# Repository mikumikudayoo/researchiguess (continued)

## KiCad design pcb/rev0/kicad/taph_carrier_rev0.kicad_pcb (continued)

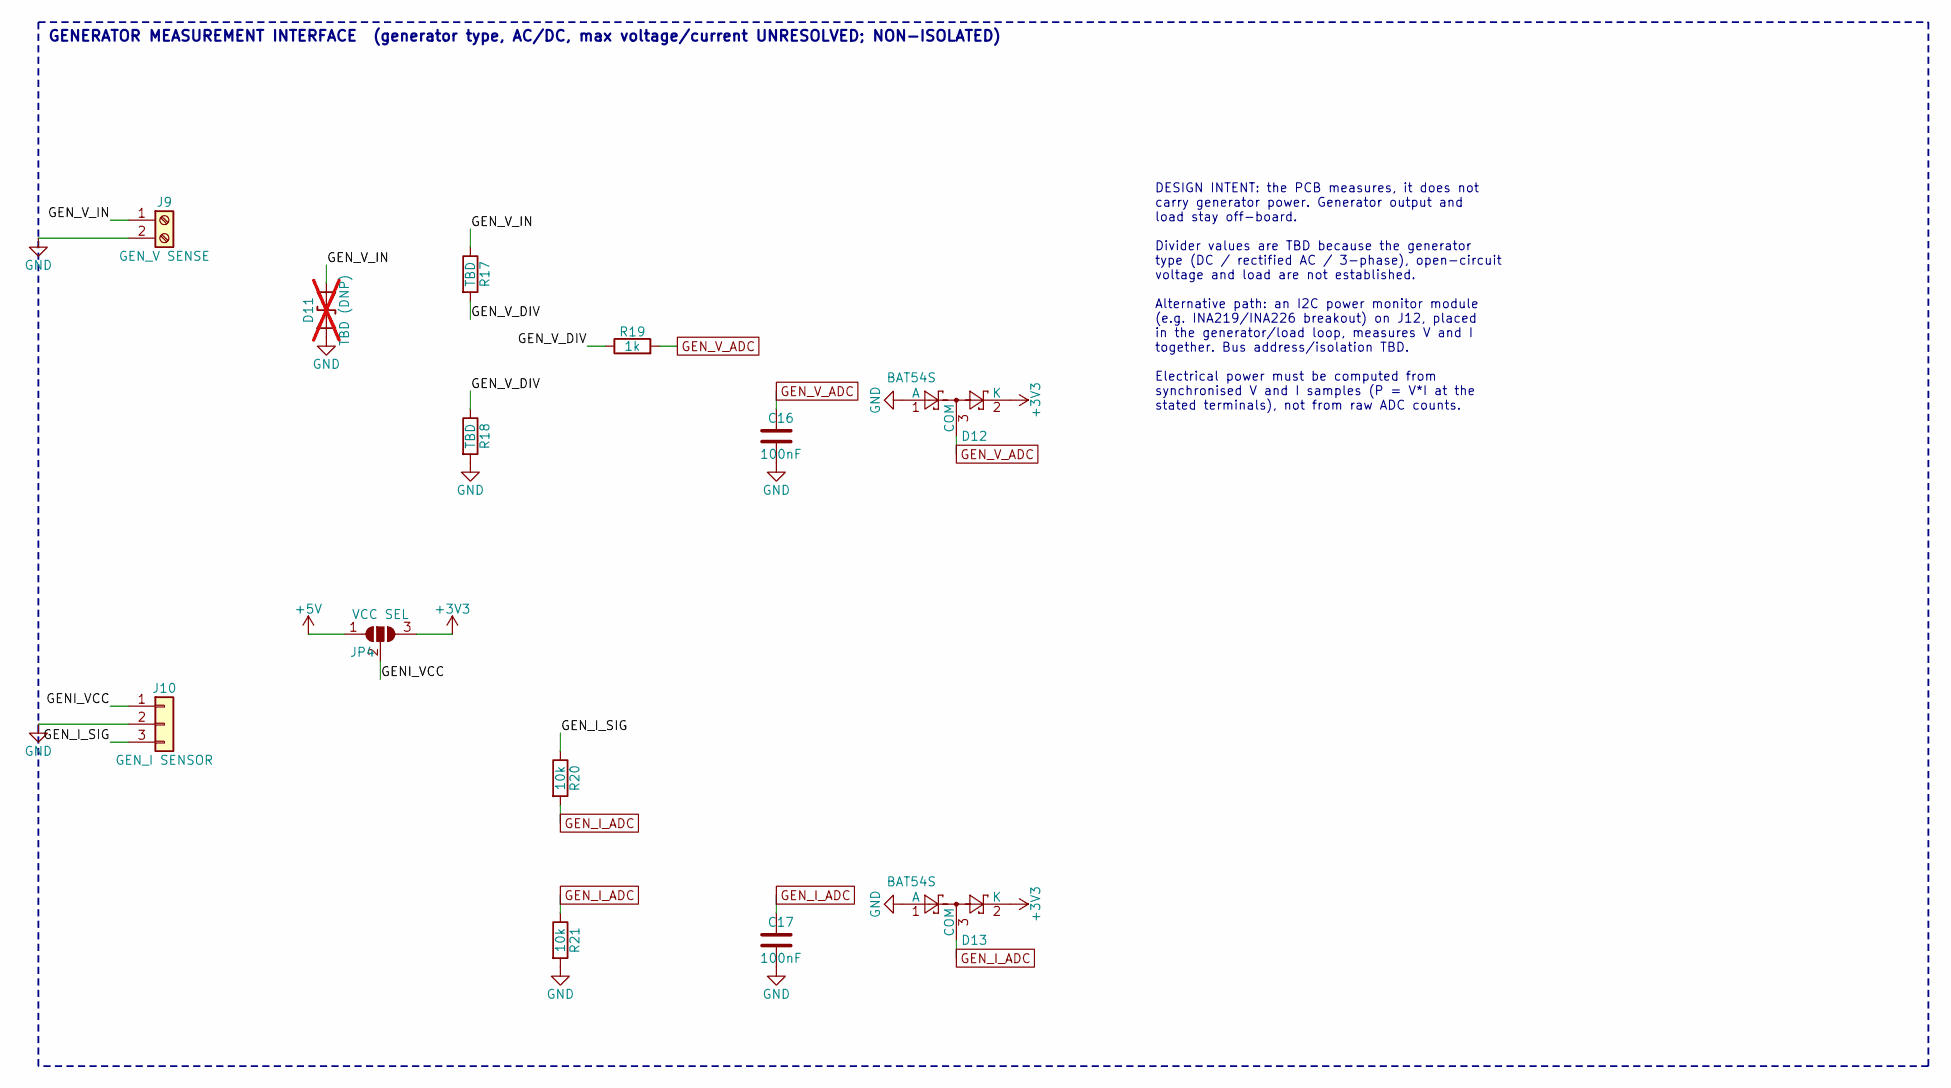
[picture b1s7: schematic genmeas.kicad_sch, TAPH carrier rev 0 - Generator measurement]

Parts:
C16, C17: 100nF; C_0805_2012Metric
D11: TBD (DNP); D_SMB; not fitted
D12, D13: BAT54S; SOT-23; MPN_candidate BAT54S (candidate)
J9: GEN_V SENSE; TerminalBlock_Phoenix_MKDS-1,5-2-5.08_1x02_P5.08mm_Horizont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; MPN_candidate Phoenix MKDS 1,5/2-5,08 (candidate)
J10: GEN_I SENSOR; JST_XH_B3B-XH-A_1x03_P2.50mm_Vertical; MPN_candidate JST XH 3-pin (candidate)
JP4: VCC SEL; SolderJumper-3_P1.3mm_Open_RoundedPad1.0x1.5mm
R17, R18: TBD; R_0805_2012Metric
R19: 1k; R_0805_2012Metric
R20, R21: 10k; R_0805_2012Metric

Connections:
+3V3: D12.2 (K), D13.2 (K), JP4.3 (B); also elsewhere on the board
+5V: JP4.1 (A); also elsewhere on the board
/Generator measurement/GENI_VCC: J10.1, JP4.2 (C)
/Generator measurement/GEN_I_SIG: J10.3, R20.1
/Generator measurement/GEN_V_DIV: R17.2, R18.1, R19.1
/Generator measurement/GEN_V_IN: D11.2 (A2), J9.1, R17.1
GEN_I_ADC: C17.1, D13.3 (COM), R20.2, R21.1; also elsewhere on the board
GEN_V_ADC: C16.1, D12.3 (COM), R19.2; also elsewhere on the board
GND: C16.2, C17.2, D11.1 (A1), D12.1 (A), D13.1 (A), J9.2, J10.2, R18.2, R21.2; also elsewhere on the board

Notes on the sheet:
GENERATOR MEASUREMENT INTERFACE (generator type, AC/DC, max voltage/current UNRESOLVED; NON-ISOLATED)
DESIGN INTENT: the PCB measures, it does not carry generator power. Generator output and load stay off-board. Divider values are TBD because the generator type (DC / rectified AC / 3-phase), open-circuit voltage and load are not established. Alternative path: an I2C power monitor module (e.g. INA21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

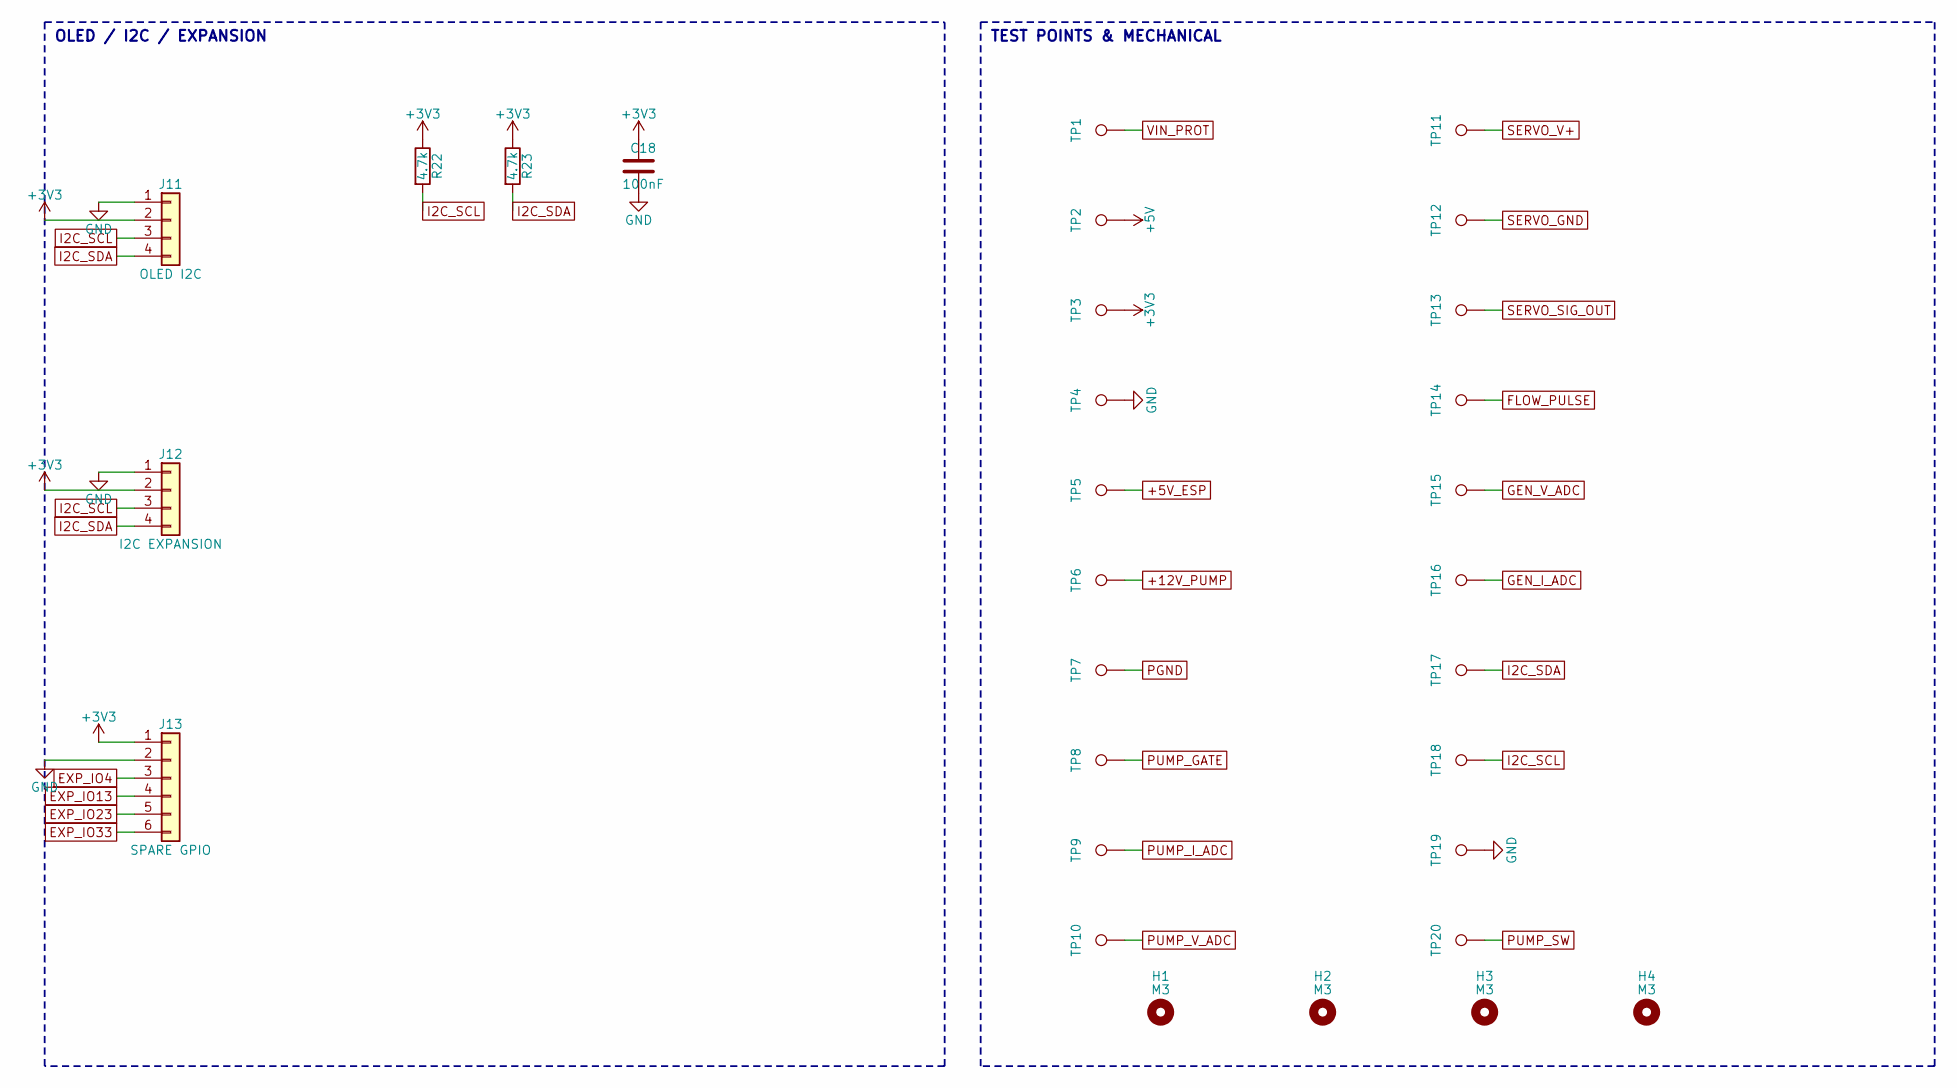
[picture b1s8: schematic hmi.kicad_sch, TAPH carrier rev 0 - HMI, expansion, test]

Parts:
C18: 100nF; C_0805_2012Metric
H1, H2, H3, H4: M3; MountingHole_3.2mm_M3
J11: OLED I2C; PinSocket_1x04_P2.54mm_Vertical; MPN_candidate 1x04 2.54 mm socket
J12: I2C EXPANSION; JST_XH_B4B-XH-A_1x04_P2.50mm_Vertical; MPN_candidate JST XH 4-pin (candidate)
J13: SPARE GPIO; PinHeader_1x06_P2.54mm_Vertical; MPN_candidate 1x06 2.54 mm header
R22, R23: 4.7k; R_0805_2012Metric
TP1: VIN_PROT; TestPoint_THTPad_D1.5mm_Drill0.7mm
TP2: +5V; TestPoint_THTPad_D1.5mm_Drill0.7mm
TP3: +3V3; TestPoint_THTPad_D1.5mm_Drill0.7mm
TP4, TP19: GND; TestPoint_THTPad_D1.5mm_Drill0.7mm
TP5: +5V_ESP; TestPoint_THTPad_D1.5mm_Drill0.7mm
TP6: +12V_PUMP; TestPoint_THTPad_D1.5mm_Drill0.7mm
TP7: PGND; TestPoint_THTPad_D1.5mm_Drill0.7mm
TP8: PUMP_GATE; TestPoint_THTPad_D1.5mm_Drill0.7mm
TP9: PUMP_I_ADC; TestPoint_THTPad_D1.5mm_Drill0.7mm
TP10: PUMP_V_ADC; TestPoint_THTPad_D1.5mm_Drill0.7mm
TP11: SERVO_V+; TestPoint_THTPad_D1.5mm_Drill0.7mm
TP12: SERVO_GND; TestPoint_THTPad_D1.5mm_Drill0.7mm
TP13: SERVO_SIG_OUT; TestPoint_THTPad_D1.5mm_Drill0.7mm
TP14: FLOW_PULSE; TestPoint_THTPad_D1.5mm_Drill0.7mm
TP15: GEN_V_ADC; TestPoint_THTPad_D1.5mm_Drill0.7mm
TP16: GEN_I_ADC; TestPoint_THTPad_D1.5mm_Drill0.7mm
TP17: I2C_SDA; TestPoint_THTPad_D1.5mm_Drill0.7mm
TP18: I2C_SCL; TestPoint_THTPad_D1.5mm_Drill0.7mm
TP20: PUMP_SW; TestPoint_THTPad_D1.5mm_Drill0.7mm

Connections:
+3V3: C18.1, J11.2, J12.2, J13.1, R22.1, R23.1, TP3.1; also elsewhere on the board
+5V: TP2.1; also elsewhere on the board
+5V_ESP: TP5.1; also elsewhere on the board
+12V_PUMP: TP6.1; also elsewhere on the board
EXP_IO4: J13.3; also elsewhere on the board
EXP_IO13: J13.4; also elsewhere on the board
EXP_IO23: J13.5; also elsewhere on the board
EXP_IO33: J13.6; also elsewhere on the board
FLOW_PULSE: TP14.1; also elsewhere on the board
GEN_I_ADC: TP16.1; also elsewhere on the board
GEN_V_ADC: TP15.1; also elsewhere on the board
GND: C18.2, J11.1, J12.1, J13.2, TP4.1, TP19.1; also elsewhere on the board
I2C_SCL: J11.3, J12.3, R22.2, TP18.1; also elsewhere on the board
I2C_SDA: J11.4, J12.4, R23.2, TP17.1; also elsewhere on the board
PGND: TP7.1; also elsewhere on the board
PUMP_GATE: TP8.1; also elsewhere on the board
PUMP_I_ADC: TP9.1; also elsewhere on the board
PUMP_SW: TP20.1; also elsewhere on the board
PUMP_V_ADC: TP10.1; also elsewhere on the board
SERVO_GND: TP12.1; also elsewhere on the board
SERVO_SIG_OUT: TP13.1; also elsewhere on the board
SERVO_V+: TP11.1; also elsewhere on the board
VIN_PROT: TP1.1; also elsewhere on the board

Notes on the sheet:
OLED / I2C / EXPANSION
TEST POINTS & MECHANICAL

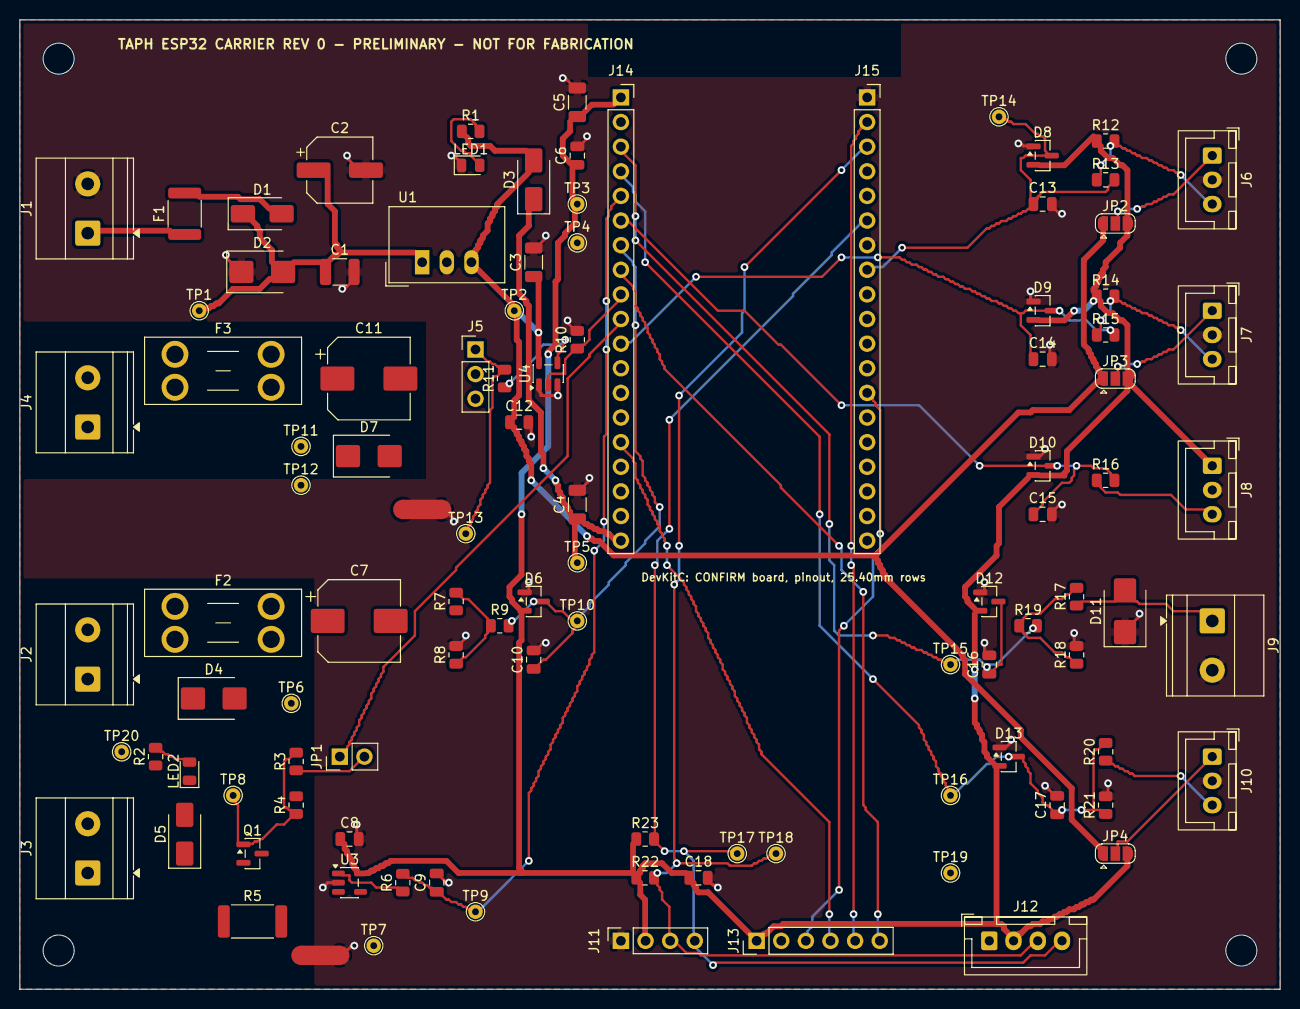
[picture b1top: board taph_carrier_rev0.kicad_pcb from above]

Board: 2 copper layers, 130.0 x 100.0 mm, 108 parts (0 on the bottom side), 47 nets.

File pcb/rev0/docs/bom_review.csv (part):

ref,sheet,kind,value,footprint,status,dnp,mpn_candidate,verification,note
J1,Logic power,component,VIN_LOGIC 12V,"TerminalBlock_Phoenix:TerminalBlock_Phoenix_MKDS-1,5-2-5.08_1x02_P5.08mm_Horizontal",PROVISIONAL,no,"Phoenix MKDS 1,5/2-5,08 (candidate)",Depends on an unverified external component; re-select after that spec is confirmed,External low-voltage DC for logic only. Supply voltage/current rating unverified. No mains on PCB.
J2,Pump switch,component,PUMP_VIN 12V,"TerminalBlock_Phoenix:TerminalBlock_Phoenix_MKDS-1,5-2-5.08_1x02_P5.08mm_Horizontal",PROVISIONAL,no,"Phoenix MKDS 1,5/2-5,08 (candidate)",Depends on an unverified external component; re-select after that spec is confirmed,"Separate pump supply input. Route through an external, reviewed isolation switch/interlock. Terminal current rating vs pump current: VERIFY."
J3,Pump switch,component,PUMP_OUT,"TerminalBlock_Phoenix:TerminalBlock_Phoenix_MKDS-1,5-2-5.08_1x02_P5.08mm_Horizontal",PROVISIONAL,no,"Phoenix MKDS 1,5/2-5,08 (candidate)",Depends on an unverified external component; re-select after that spec is confirmed,"To external 12 V pump (+ / -). Pump model, current and inrush unverified."
J4,Servo interface,component,SERVO_VIN,"TerminalBlock_Phoenix:TerminalBlock_Phoenix_MKDS-1,5-2-5.08_1x02_P5.08mm_Horizontal",PROVISIONAL,no,"Phoenix MKDS 1,5/2-5,08 (candidate)",Depends on an unverified external component; re-select after that spec is confirmed,Dedicated servo supply (voltage per actual servo datasheet). Removable for actuator isolation.
J5,Servo interface,component,"SERVO (S,+,-)",Connector_PinHeader_2.54mm:PinHeader_1x03_P2.54mm_Vertical,CONFIRM,no,,Pinout/mechanical mapping must be checked against the physical part,"Common hobby-servo order S,+,-; CONFIRM against actual servo lead. 2.54 mm pin current vs stall current unverified."
J6,Sensor inputs,component,FLOW SENSOR,Connector_JST:JST_XH_B3B-XH-A_1x03_P2.50mm_Vertical,CONFIRM,no,JST XH 3-pin (candidate),Pinout/mechanical mapping must be checked against the physical part,"Pin 1 sensor supply, 2 GND, 3 signal. CONFIRM sensor lead mapping."
J7,Sensor inputs,component,RPM SENSOR (opt),Connector_JST:JST_XH_B3B-XH-A_1x03_P2.50mm_Vertical,OPTIONAL,no,JST XH 3-pin (candidate),Populate only if this interface is adopted,"Pin 1 sensor supply, 2 GND, 3 signal. CONFIRM sensor lead mapping."
J8,Sensor inputs,component,PITCH FB (opt),Connector_JST:JST_XH_B3B-XH-A_1x03_P2.50mm_Vertical,OPTIONAL,no,JST XH 3-pin (candidate),Populate only if this interface is adopted,Ratiometric potentiometer / sensor powered from +3V3. Mechanism and sensor unresolved.
J9,Generator measurement,component,GEN_V SENSE,"TerminalBlock_Phoenix:TerminalBlock_Phoenix_MKDS-1,5-2-5.08_1x02_P5.08mm_Horizontal",PROVISIONAL,no,"Phoenix MKDS 1,5/2-5,08 (candidate)",Depends on an unverified external component; re-select after that spec is confirmed,Sense-only connection (no generator power flows through PCB). Pin 2 is board GND: generator/load negative becomes bonded to logic ground - REVIEW.
J10,Generator measurement,component,GEN_I SENSOR,Connector_JST:JST_XH_B3B-XH-A_1x03_P2.50mm_Vertical,PROVISIONAL,no,JST XH 3-pin (candidate),Depends on an unverified external component; re-select after that spec is confirmed,For an OFF-BOARD current sensor module in the generator/load loop (e.g. hall-effect). Sensor model and range TBD.
J11,"HMI, expansion, test",component,OLED I2C,Connector_PinSocket_2.54mm:PinSocket_1x04_P2.54mm_Vertical,CONFIRM,no,1x04 2.54 mm socket,Pinout/mechanical mapping must be checked against the physical part,"Common SSD1306 128x64 module order GND,VCC,SCL,SDA - many modules swap GND/VCC: CONFIRM before insertion."
J12,"HMI, expansion, test",component,I2C EXPANSION,Connector_JST:JST_XH_B4B-XH-A_1x04_P2.50mm_Vertical,OPTIONAL,no,JST XH 4-pin (candidate),Populate only if this interface is adopted,For off-board I2C power monitor (generator or pump). Long cables: add bus buffer - TBD.
J13,"HMI, expansion, test",component,SPARE GPIO,Connector_PinHeader_2.54mm:PinHeader_1x06_P2.54mm_Vertical,OPTIONAL,no,1x06 2.54 mm header,Populate only if this interface is adopted,"Uncommitted 3.3 V GPIO, unprotected - bench use only"
J14,ESP32 DevKitC socket,component,DevKitC J2 socket,Connector_PinSocket_2.54mm:PinSocket_1x19_P2.54mm_Vertical,CONFIRM,no,2.54 mm 1x19 female header,Pinout/mechanical mapping must be checked against the physical part,Pin order per Espressif DevKitC V4 guide; clone boards differ. Row spacing on PCB = 25.40 mm (CONFIRM).
J15,ESP32 DevKitC socket,component,DevKitC J3 socket,Connector_PinSocket_2.54mm:PinSocket_1x19_P2.54mm_Vertical,CONFIRM,no,2.54 mm 1x19 female header,Pinout/mechanical mapping must be checked against the physical part,Pin order per Espressif DevKitC V4 guide; clone boards differ.
JP1,Pump switch,component,PUMP_HW_ENABLE,Connector_PinHeader_2.54mm:PinHeader_1x02_P2.54mm_Vertical,IMPLEMENTED,no,2-pin header + shunt,Circuit function chosen; candidate part/rating still to be checked against datasheet,Hardware disable: remove shunt => gate held off by R4 regardless of firmware.
U1,Logic power,component,TSR 1-2450,Converter_DCDC:Converter_DCDC_TRACO_TSR-1_THT,PROVISIONAL,no,TRACO TSR 1-2450 (candidate),Depends on an unverified external component; re-select after that spec is confirmed,Drop-in 5 V 1 A switching regulator module; input range/derating to be re-verified from current datasheet
U3,Pump switch,component,INA180A1,Package_TO_SOT_SMD:SOT-23-5,PROVISIONAL,no,TI INA180A1 (candidate),Depends on an unverified external component; re-select after that spec is confirmed,Low-side current-sense amplifier; gain suffix (A1..A4) chosen with shunt value.
U4,Servo interface,component,74AHCT1G125,Package_TO_SOT_SMD:SOT-23-5,IMPLEMENTED,no,74AHCT1G125 SOT-23-5 (candidate),Circuit function chosen; candidate part/rating still to be checked against datasheet,3.3 V -> 5 V servo signal buffer (TTL-threshold input). OE tied active.
Q1,Pump switch,component,AO3400A,Package_TO_SOT_SMD:SOT-23,PROVISIONAL,no,AO3400A (candidate),Depends on an unverified external component; re-select after that spec is confirmed,"Logic-level N-MOSFET, low side. Adequacy (Rds(on) at Vgs=3.3 V, SOT-23 dissipation) depends on unverified pump current."
D1,Logic power,component,SS34,Diode_SMD:D_SMA,IMPLEMENTED,no,"SS34 (candidate, 40 V 3 A class - verify)",Circuit function chosen; candidate part/rating still to be checked against datasheet,Series reverse-polarity protection for logic input (approx. 0.4-0.5 V drop)
D2,Logic power,component,SMBJ18CA,Diode_SMD:D_SMB,PROVISIONAL,no,SMBJ18CA (candidate - verify clamp vs U1 abs. max),Depends on an unverified external component; re-select after that spec is confirmed,Bidirectional TVS; standoff must exceed max supply voltage incl. charger/float voltage
D3,Logic power,component,SS14,Diode_SMD:D_SMA,IMPLEMENTED,no,SS14 (candidate),Circuit function chosen; candidate part/rating still to be checked against datasheet,Prevents carrier +5V and DevKitC USB VBUS from back-feeding each other via the DevKitC 5V pin. Verify DevKitC's own VBUS protection.
D4,Pump switch,component,SMBJ18CA,Diode_SMD:D_SMB,PROVISIONAL,no,SMBJ18CA (candidate),Depends on an unverified external component; re-select after that spec is confirmed,
D5,Pump switch,component,SS34,Diode_SMD:D_SMA,IMPLEMENTED,no,SS34 (candidate),Circuit function chosen; candidate part/rating still to be checked against datasheet,Freewheel diode across inductive pump load
D6,Pump switch,component,BAT54S,Package_TO_SOT_SMD:SOT-23,IMPLEMENTED,no,BAT54S (candidate),Circuit function chosen; candidate part/rating still to be checked against datasheet,Schottky clamp of ADC/GPIO node to GND and +3V3; leakage adds ADC error - characterise
D7,Servo interface,component,TBD (DNP),Diode_SMD:D_SMB,DNP,yes,,Footprint reserved; do not populate in rev 0,Standoff voltage depends on servo supply voltage
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
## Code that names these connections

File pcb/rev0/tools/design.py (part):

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    Part("C1", "Device:C", "10uF 50V X7R", FP_C1210, 109.22, 60.96, 0,
         {"1": "VIN_PROT", "2": "GND"}, "IMPLEMENTED", "", "Input ceramic per U1 datasheet recommendation (verify)"),
    Part("C2", "Device:C_Polarized", "47uF 35V", "Capacitor_SMD:CP_Elec_6.3x7.7", 121.92, 60.96, 0,
         {"1": "VIN_PROT", "2": "GND"}, "IMPLEMENTED", "", "Bulk/damping for cable inductance"),
    Part("U1", "Converter_DCDC:TSR_1-2450", "TSR 1-2450", "Converter_DCDC:Converter_DCDC_TRACO_TSR-1_THT", 154.94, 55.88, 0,
         {"1": "VIN_PROT", "2": "GND", "3": "+5V"}, "PROVISIONAL", "TRACO TSR 1-2450 (candidate)",
         "Drop-in 5 V 1 A switching regulator module; input range/derating to be re-verified from current datasheet"),
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         {"1": "PUMP_GATE", "2": "PUMP_SRC", "3": "PUMP_SW"}, "PROVISIONAL", "AO3400A (candidate)",
         "Logic-level N-MOSFET, low side. Adequacy (Rds(on) at Vgs=3.3 V, SOT-23 dissipation) depends on unverified pump current."),
    Part("JP1", "Jumper:Jumper_2_Open", "PUMP_HW_ENABLE", "Connector_PinHeader_2.54mm:PinHeader_1x02_P2.54mm_Vertical",
         147.32, 88.9, 0, {"1": "PUMP_EN", "2": "PUMP_EN_J"}, "IMPLEMENTED", "2-pin header + shunt",
         "Hardware disable: remove shunt => gate held off by R4 regardless of firmware."),
    Part("R3", "Device:R", "100", FP_R, 187.96, 88.9, 90, {"1": "PUMP_EN_J", "2": "PUMP_GATE"}, "IMPLEMENTED",
         "", "Gate series resistor"),
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pulse_input(S, 88.9, "J7", "JP3", "R14", "R15", "C14", "D9", "RPM_SIG", "RPM_PULSE", "RPM_VCC", "RPM SENSOR (opt)", "OPTIONAL")
S.parts += [
    Part("J8", "Connector_Generic:Conn_01x03", "PITCH FB (opt)", FP_XH3, 33.02, 132.08, 0,
         {"1": "+3V3", "2": "GND", "3": "PITCH_FB_SIG"}, "OPTIONAL", "JST XH 3-pin (candidate)",
         "Ratiometric potentiometer / sensor powered from +3V3. Mechanism and sensor unresolved."),
    Part("R16", "Device:R", "1k", FP_R, 124.46, 134.62, 90, {"1": "PITCH_FB_SIG", "2": "PITCH_FB_ADC"}, "OPTIONAL"),
    Part("C15", "Device:C", "100nF", FP_C, 149.86, 144.78, 0, {"1": "PITCH_FB_ADC", "2": "GND"}, "OPTIONAL"),
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    Part("R19", "Device:R", "1k", FP_R, 99.06, 63.5, 90, {"1": "GEN_V_DIV", "2": "GEN_V_ADC"}, "IMPLEMENTED"),
    Part("C16", "Device:C", "100nF", FP_C, 119.38, 76.2, 0, {"1": "GEN_V_ADC", "2": "GND"}, "IMPLEMENTED"),
    Part("J10", "Connector_Generic:Conn_01x03", "GEN_I SENSOR", FP_XH3, 33.02, 116.84, 0,
         {"1": "GENI_VCC", "2": "GND", "3": "GEN_I_SIG"}, "PROVISIONAL", "JST XH 3-pin (candidate)",
         "For an OFF-BOARD current sensor module in the generator/load loop (e.g. hall-effect). Sensor model and range TBD."),
    Part("JP4", "Jumper:SolderJumper_3_Open", "VCC SEL", FP_SJ3, 63.5, 104.14, 0,
         {"1": "+5V", "2": "GENI_VCC", "3": "+3V3"}, "CONFIRM", "", "Ships OPEN; set per sensor supply spec", in_bom=False),
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    Part("R23", "Device:R", "4.7k", FP_R, 81.28, 38.1, 0, {"1": "+3V3", "2": "I2C_SDA"}, "IMPLEMENTED"),
    Part("C18", "Device:C", "100nF", FP_C, 99.06, 38.1, 0, {"1": "+3V3", "2": "GND"}, "IMPLEMENTED"),
    Part("J12", "Connector_Generic:Conn_01x04", "I2C EXPANSION", FP_XH4, 33.02, 83.82, 0,
         {"1": "GND", "2": "+3V3", "3": "I2C_SCL", "4": "I2C_SDA"}, "OPTIONAL", "JST XH 4-pin (candidate)",
         "For off-board I2C power monitor (generator or pump). Long cables: add bus buffer - TBD."),
    Part("J13", "Connector_Generic:Conn_01x06", "SPARE GPIO", "Connector_PinHeader_2.54mm:PinHeader_1x06_P2.54mm_Vertical",
         33.02, 124.46, 0, {"1": "+3V3", "2": "GND", "3": "EXP_IO4", "4": "EXP_IO13", "5": "EXP_IO23", "6": "EXP_IO33"},
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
